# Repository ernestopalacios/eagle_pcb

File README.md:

eagle_pcb
=========

Diseños de placas

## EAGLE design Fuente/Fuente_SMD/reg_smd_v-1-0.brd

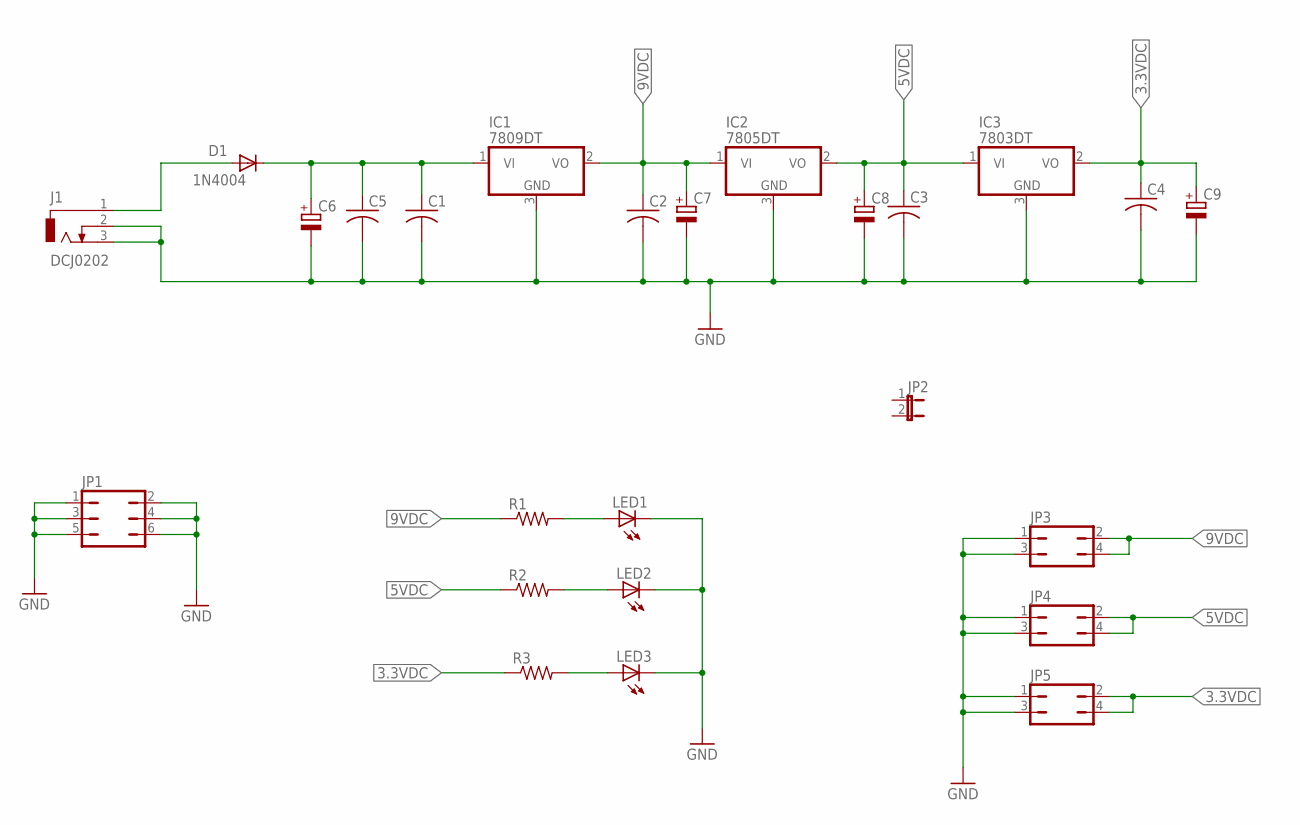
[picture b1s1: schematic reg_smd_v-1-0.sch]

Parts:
C1, C2, C3, C4, C5: C-USC1206; C1206
C6, C7, C8, C9: CPOL-EUE2.5-6; E2,5-6
D1: 1N4004; DO41-10
IC1: 7809DT; TO252
IC2: 7805DT; TO252
IC3: 7803DT; TO252
J1: DCJ0202
JP1: JP3Q
JP2: JP1E; JP1
JP3, JP4, JP5: JP2Q
LED1, LED2, LED3: LEDCHIPLED_1206; CHIPLED_1206
R1, R2, R3: R-US_M1206; M1206

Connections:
3.3VDC: C4.1, C9.+, IC3.2 (VO), JP5.2, JP5.4, R3.1
5VDC: C3.1, C8.+, IC2.2 (VO), IC3.1 (VI), JP4.2, JP4.4, R2.1
9VDC: C2.1, C7.+, IC1.2 (VO), IC2.1 (VI), JP3.2, JP3.4, R1.1
GND: C1.2, C2.2, C3.2, C4.2, C5.2, C6.-, C7.-, C8.-, C9.-, IC1.3 (GND), IC2.3 (GND), IC3.3 (GND), J1.2, J1.3, JP1.1, JP1.2, JP1.3, JP1.4, JP1.5, JP1.6, JP3.1, JP3.3, JP4.1, JP4.3, JP5.1, JP5.3, LED1.C, LED2.C, LED3.C
unnamed: LED1.A, R1.2
unnamed: LED2.A, R2.2
unnamed: LED3.A, R3.2
unnamed: D1.A, J1.1
unnamed: C1.1, C5.1, C6.+, D1.C, IC1.1 (VI)

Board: 2 copper layers, 25 parts (0 on the bottom side), 9 nets, no tracks yet.

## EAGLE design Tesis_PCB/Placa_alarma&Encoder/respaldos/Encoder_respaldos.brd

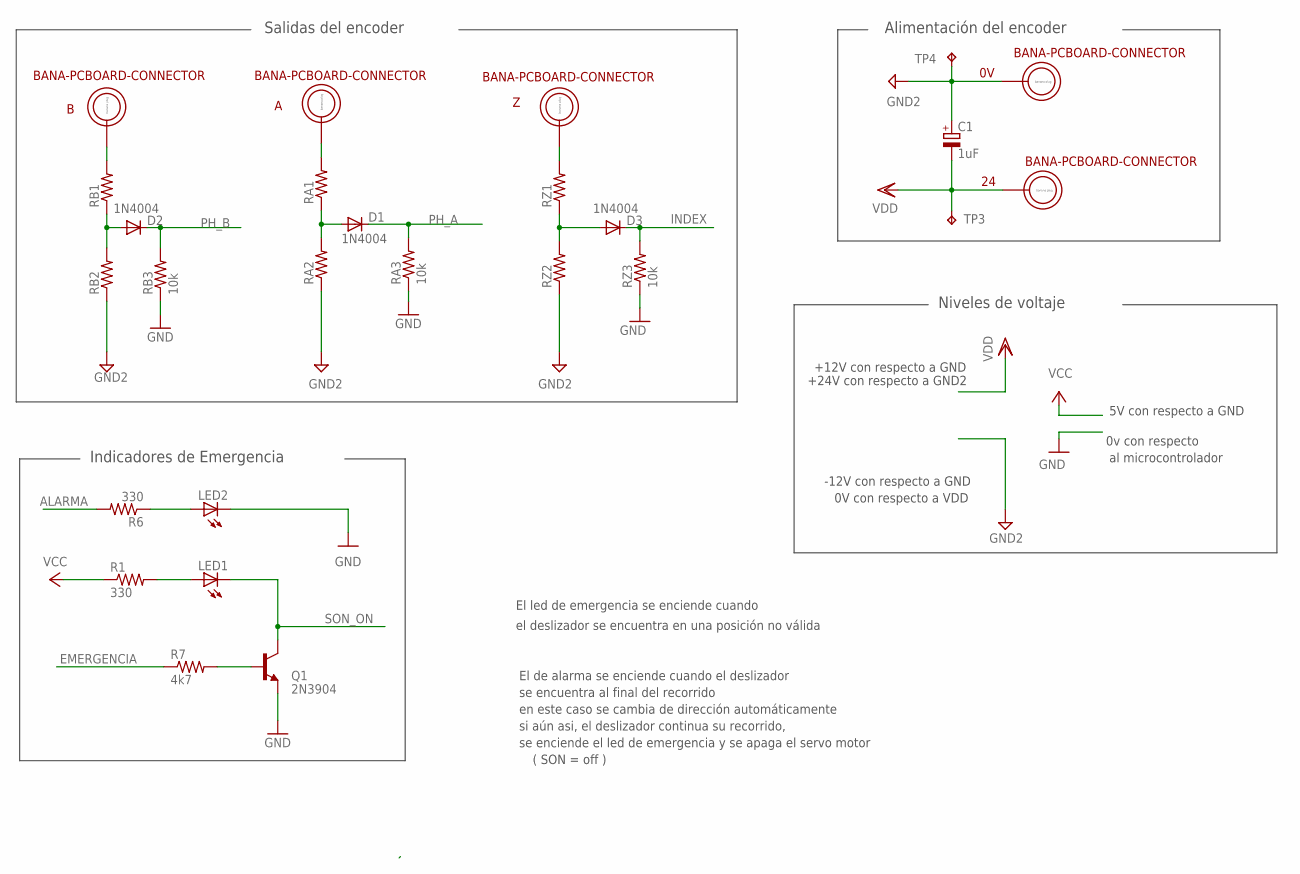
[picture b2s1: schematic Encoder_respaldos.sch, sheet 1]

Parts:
0V, 24: BANA-PCBOARD-CONNECTOR; BANA_PLUG
A: BANA-PCBOARD-CONNECTOR; BANA_PLUG
B: BANA-PCBOARD-CONNECTOR; BANA_PLUG
C1: 1uF; E2,5-6
D1, D2, D3: 1N4004; DO41-10
LED1, LED2: LED5MM
Q1: 2N3904; TO92
R1, R6: 330; 0204/7
R7: 4k7; 0204/7
RA1, RA2: R-US_0204/7; 0204/7
RA3: 10k; 0204/7
RB1, RB2: R-US_0204/7; 0204/7
RB3: 10k; 0204/7
RZ1, RZ2: R-US_0204/7; 0204/7
RZ3: 10k; 0204/7
TP3, TP4: TPB2,54; B2,54
Z: BANA-PCBOARD-CONNECTOR; BANA_PLUG

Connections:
ALARMA: R6.2; also elsewhere on the board
EMERGENCIA: R7.1; also elsewhere on the board
GND: LED2.K (C), Q1.3 (E), RA3.1, RB3.1, RZ3.1; also elsewhere on the board
GND2: 0V.P$1, C1.+, RA2.1, RB2.1, RZ2.1, TP4.TP; also elsewhere on the board
INDEX: D3.C, RZ3.2; also elsewhere on the board
unnamed: Q1.2 (B), R7.2
unnamed: LED1.A, R1.2
unnamed: LED2.A, R6.1
unnamed: D1.A, RA1.1, RA2.2
unnamed: D2.A, RB1.1, RB2.2
unnamed: RZ1.2, Z.P$1
unnamed: B.P$1, RB1.2
unnamed: A.P$1, RA1.2
unnamed: D3.A, RZ1.1, RZ2.2
PH_A: D1.C, RA3.2; also elsewhere on the board
PH_B: D2.C, RB3.2; also elsewhere on the board
SON_ON: LED1.K (C), Q1.1 (C); also elsewhere on the board
VCC: R1.1; also elsewhere on the board
VDD: 24.P$1, C1.-, TP3.TP; also elsewhere on the board

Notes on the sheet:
0v con respecto
5V con respecto a GND
+12V con respecto a GND
+24V con respecto a GND2
-12V con respecto a GND
0V con respecto a VDD
El led de emergencia se enciende cuando
el deslizador se encuentra en una posición no válida
El de alarma se enciende cuando el deslizador
se encuentra al final del recorrido
en este caso se cambia de dirección automáticamente
si aún asi, el deslizador continua su recorrido,
se enciende el led de emergencia y se apaga el servo motor
( SON = off )
Indicadores de Emergencia
Salidas del encoder
Alimentación del encoder
Niveles de voltaje
al microcontrolador

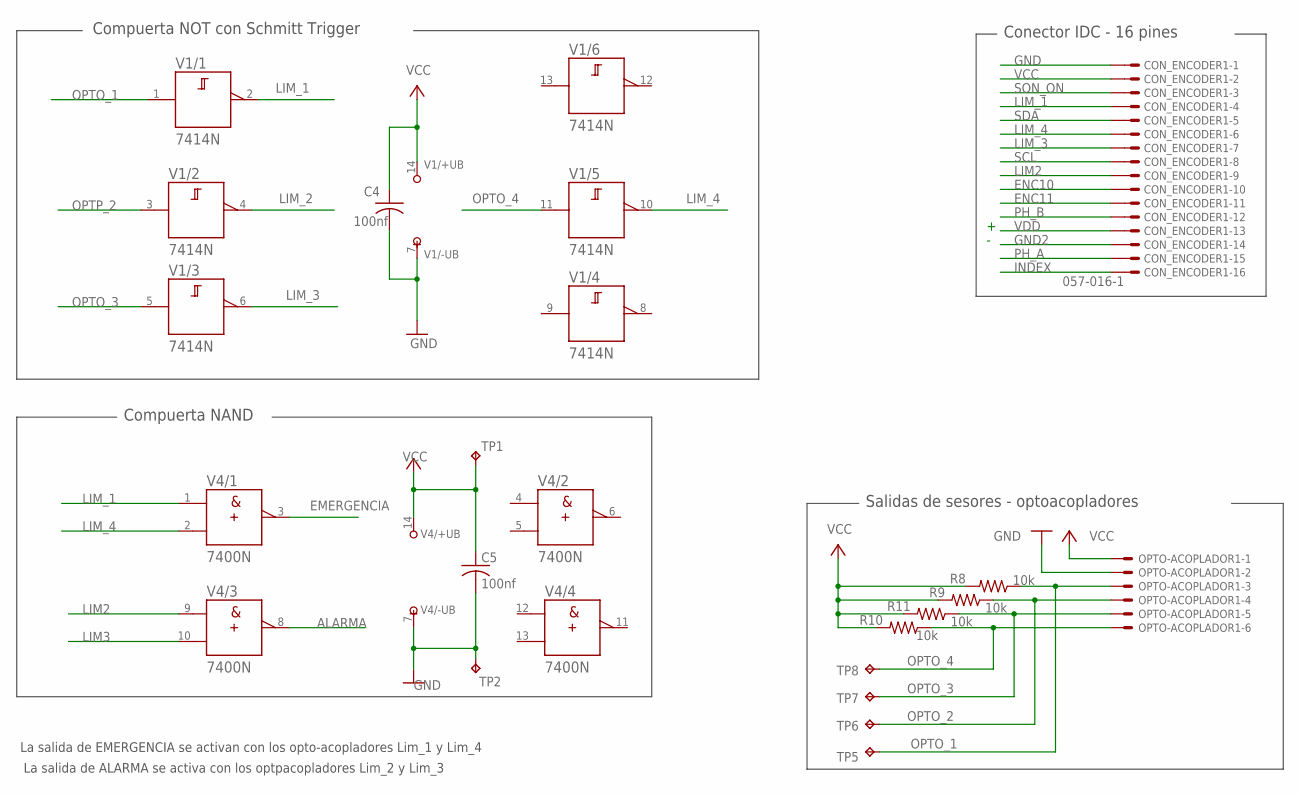
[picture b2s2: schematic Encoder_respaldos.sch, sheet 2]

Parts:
C4, C5: 100nf; C025-024X044
CON_ENCODER1: 057-016-1
OPTO-ACOPLADOR1: 22-23-2061
R8, R9, R10, R11: 10k; 0204/7
TP1, TP2, TP5, TP6, TP7, TP8: TPB2,54; B2,54
V1: 7414N; DIL14
V4: 7400N; DIL14

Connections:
ALARMA: V4.8 (Y); also elsewhere on the board
EMERGENCIA: V4.3 (Y); also elsewhere on the board
ENC10: CON_ENCODER1.10
ENC11: CON_ENCODER1.11
GND: C4.2, C5.2, CON_ENCODER1.1, OPTO-ACOPLADOR1.2, TP2.TP, V1.7 (-UB), V4.7 (-UB); also elsewhere on the board
GND2: CON_ENCODER1.14; also elsewhere on the board
INDEX: CON_ENCODER1.16; also elsewhere on the board
LIM2: CON_ENCODER1.9, V4.9 (A)
LIM3: V4.10 (B)
LIM_1: CON_ENCODER1.4, V1.2 (Y), V4.1 (A)
LIM_2: V1.4 (Y)
LIM_3: CON_ENCODER1.7, V1.6 (Y)
LIM_4: CON_ENCODER1.6, V1.10 (Y), V4.2 (B)
OPTO_1: OPTO-ACOPLADOR1.3, R8.1, TP5.TP, V1.1 (A)
OPTO_2: OPTO-ACOPLADOR1.4, R9.1, TP6.TP
OPTO_3: OPTO-ACOPLADOR1.5, R11.1, TP7.TP, V1.5 (A)
OPTO_4: OPTO-ACOPLADOR1.6, R10.1, TP8.TP, V1.11 (A)
OPTP_2: V1.3 (A)
PH_A: CON_ENCODER1.15; also elsewhere on the board
PH_B: CON_ENCODER1.12; also elsewhere on the board
SCL: CON_ENCODER1.8
SDA: CON_ENCODER1.5
SON_ON: CON_ENCODER1.3; also elsewhere on the board
VCC: C4.1, C5.1, CON_ENCODER1.2, OPTO-ACOPLADOR1.1, R8.2, R9.2, R10.2, R11.2, TP1.TP, V1.14 (+UB), V4.14 (+UB); also elsewhere on the board
VDD: CON_ENCODER1.13; also elsewhere on the board

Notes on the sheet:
Compuerta NAND
Compuerta NOT con Schmitt Trigger
Conector IDC - 16 pines
Salidas de sesores - optoacopladores
La salida de EMERGENCIA se activan con los opto-acopladores Lim_1 y Lim_4
La salida de ALARMA se activa con los optpacopladores Lim_2 y Lim_3

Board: 2 copper layers, 42 parts (0 on the bottom side), 27 nets, no tracks yet.

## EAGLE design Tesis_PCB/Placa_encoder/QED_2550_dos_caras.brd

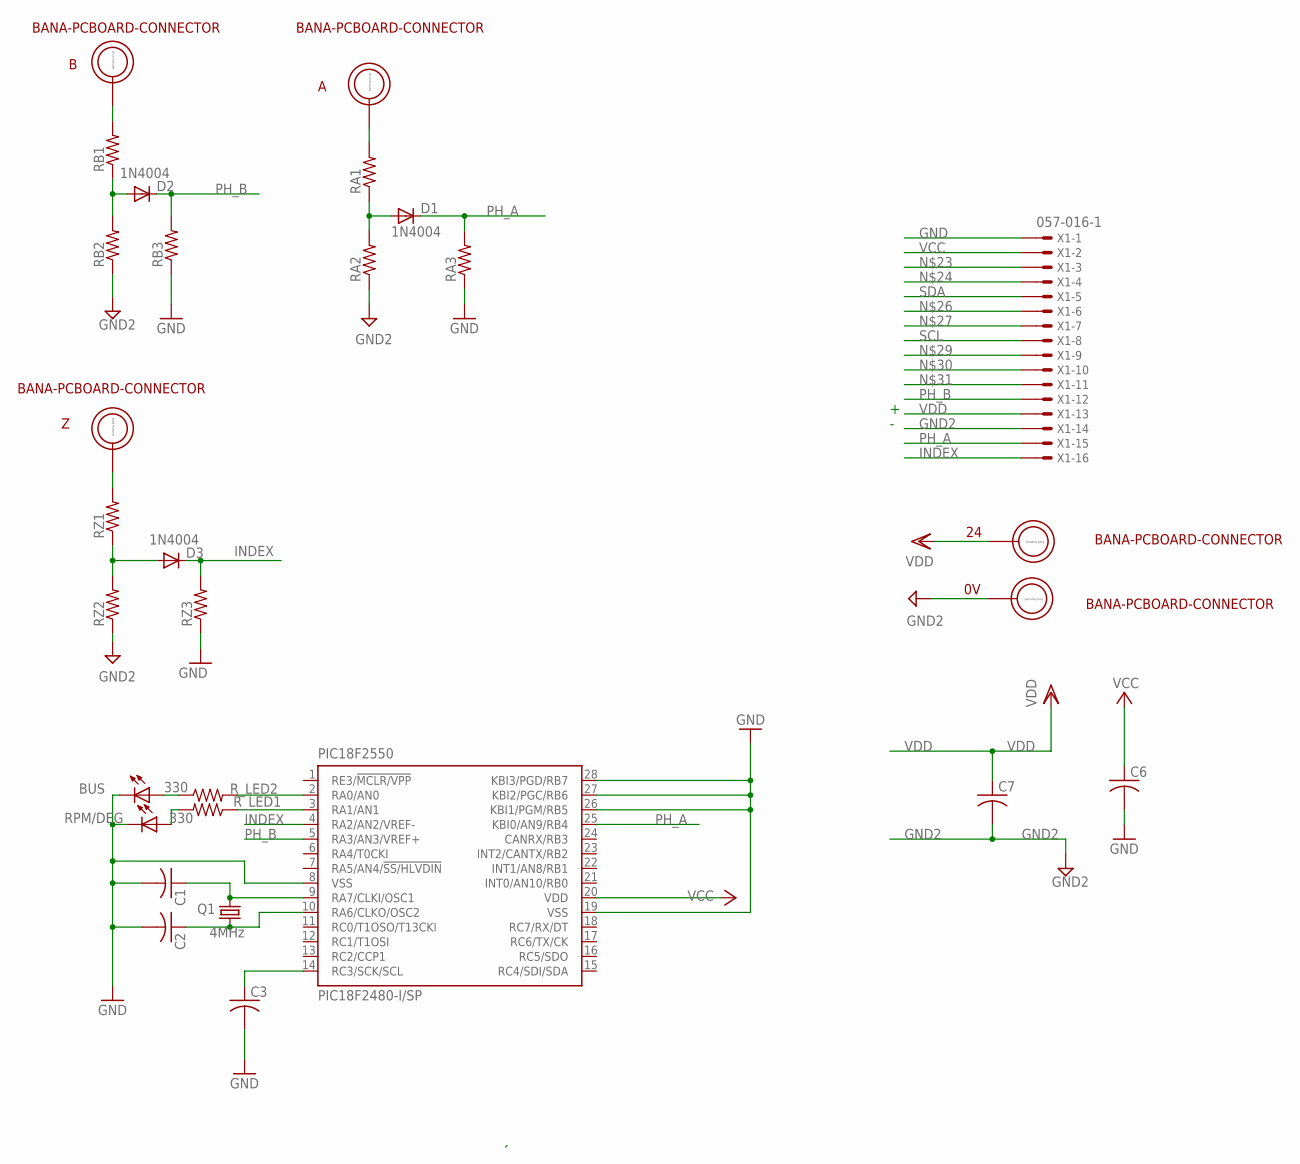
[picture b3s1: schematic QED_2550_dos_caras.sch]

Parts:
0V, 24: BANA-PCBOARD-CONNECTOR; BANA_PLUG
A: BANA-PCBOARD-CONNECTOR; BANA_PLUG
B: BANA-PCBOARD-CONNECTOR; BANA_PLUG
BUS: LED5MM
C1, C2, C3: C-US025-024X044; C025-024X044
C6, C7: C-US025-030X050; C025-030X050
D1, D2, D3: 1N4004; DO41-10
PIC18F2550: PIC18F2480-I/SP; DIL28-3
Q1: 4MHz; HC49/S
RA1, RA2, RA3: R-US_0204/7; 0204/7
RB1, RB2, RB3: R-US_0204/7; 0204/7
RPM/DEG: LED5MM
RZ1, RZ2, RZ3: R-US_0204/7; 0204/7
R_LED1, R_LED2: 330; 0204/7
X1: 057-016-1
Z: BANA-PCBOARD-CONNECTOR; BANA_PLUG

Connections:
GND: BUS.K (C), C1.2, C2.2, C3.2, C6.2, PIC18F2550.8 (VSS), PIC18F2550.19 (VSS), PIC18F2550.26 (KBI1/PGM/RB5), PIC18F2550.27 (KBI2/PGC/RB6), PIC18F2550.28 (KBI3/PGD/RB7), RA3.1, RB3.1, RPM/DEG.K (C), RZ3.1, X1.1
GND2: 0V.P$1, C7.2, RA2.1, RB2.1, RZ2.1, X1.14
INDEX: D3.C, PIC18F2550.4 (RA2/AN2/VREF-), RZ3.2, X1.16
unnamed: C1.1, PIC18F2550.9 (RA7/CLKI/OSC1), Q1.2
unnamed: C2.1, PIC18F2550.10 (RA6/CLKO/OSC2), Q1.1
unnamed: C3.1, PIC18F2550.14 (RC3/SCK/SCL)
unnamed: PIC18F2550.2 (RA0/AN0), R_LED2.2
unnamed: BUS.A, R_LED2.1
unnamed: PIC18F2550.3 (RA1/AN1), R_LED1.1
unnamed: RPM/DEG.A, R_LED1.2
unnamed: D1.A, RA1.1, RA2.2
unnamed: D2.A, RB1.1, RB2.2
unnamed: RZ1.2, Z.P$1
unnamed: B.P$1, RB1.2
unnamed: A.P$1, RA1.2
unnamed: D3.A, RZ1.1, RZ2.2
PH_A: D1.C, PIC18F2550.25 (KBI0/AN9/RB4), RA3.2, X1.15
PH_B: D2.C, PIC18F2550.5 (RA3/AN3/VREF+), RB3.2, X1.12
SCL: X1.8
SDA: X1.5
VCC: C6.1, PIC18F2550.20 (VDD), X1.2
VDD: 24.P$1, C7.1, X1.13

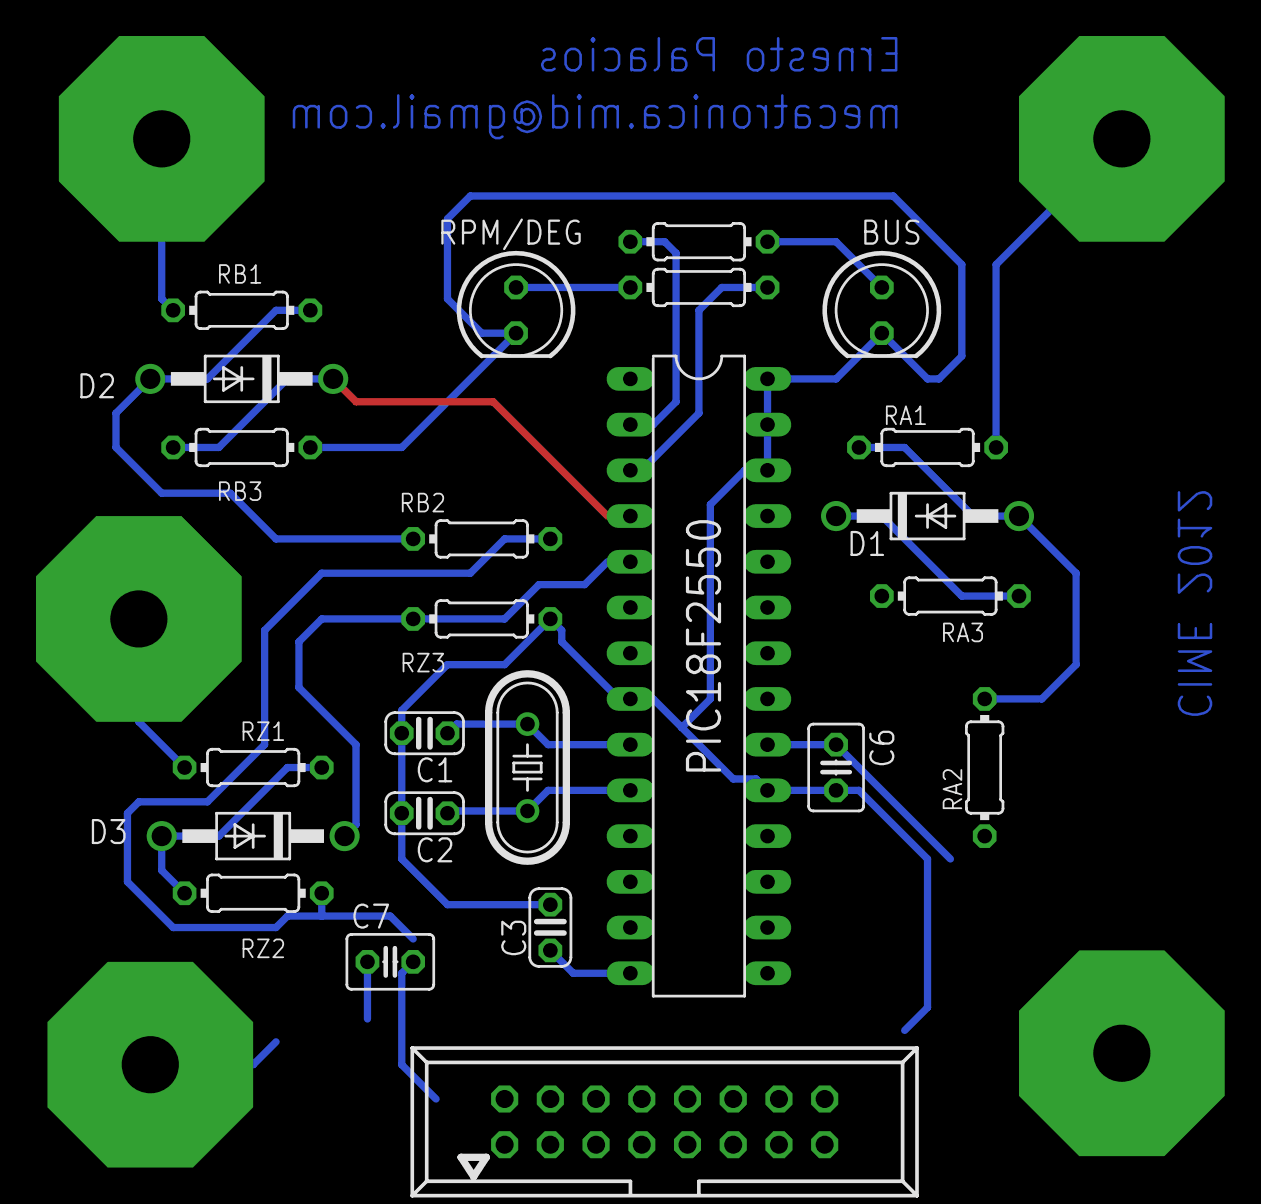
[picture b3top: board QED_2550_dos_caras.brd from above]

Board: 2 copper layers, 29 parts (0 on the bottom side), 20 nets.

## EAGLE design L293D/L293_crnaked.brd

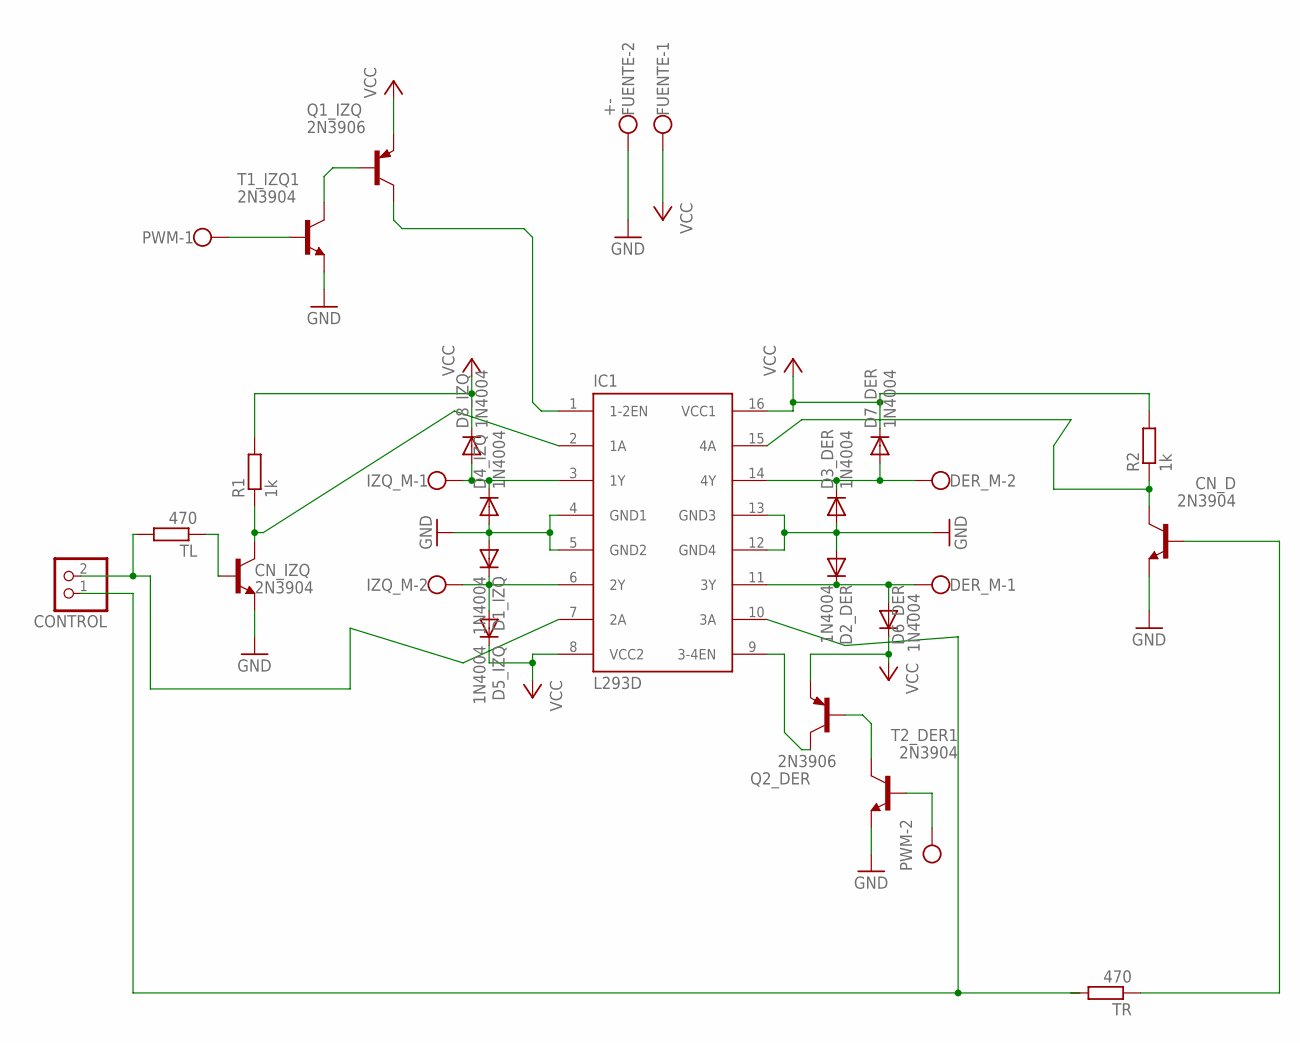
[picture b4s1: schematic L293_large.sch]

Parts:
CN_D: 2N3904; TO92
CN_IZQ: 2N3904; TO92
CONTROL: PINHD-1X2/90; 1X02/90
D1_IZQ, D2_DER, D3_DER, D4_IZQ, D5_IZQ, D6_DER, D7_DER, D8_IZQ: 1N4004; DO41-10
DER_M: W237-02P; W237-132
FUENTE: +-; W237-132
IC1: L293D; DIL16
IZQ_M: W237-02P; W237-132
PWM: W237-02P; W237-132
Q1_IZQ, Q2_DER: 2N3906; TO92
R1, R2: 1k; 0207/5V
T1_IZQ1, T2_DER1: 2N3904; TO92
TL: 470; 0207/5V
TR: 470; 0207/5V

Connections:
GND: CN_D.3 (E), CN_IZQ.3 (E), D1_IZQ.A, D2_DER.A, D3_DER.A, D4_IZQ.A, FUENTE.2, IC1.4 (GND1), IC1.5 (GND2), IC1.12 (GND4), IC1.13 (GND3), T1_IZQ1.3 (E), T2_DER1.3 (E); also elsewhere on the board
unnamed: D2_DER.C, D6_DER.A, DER_M.1, IC1.11 (3Y)
unnamed: D3_DER.C, D7_DER.A, DER_M.2, IC1.14 (4Y)
unnamed: D1_IZQ.C, D5_IZQ.A, IC1.6 (2Y), IZQ_M.2
unnamed: D4_IZQ.C, D8_IZQ.A, IC1.3 (1Y), IZQ_M.1
unnamed: CONTROL.2, IC1.7 (2A), TL.2
unnamed 6: CN_IZQ.2 (B), TL.1; also elsewhere on the board
unnamed 7: CN_IZQ.1 (C), IC1.2 (1A), R1.1; also elsewhere on the board
unnamed 8: CN_D.2 (B), TR.1; also elsewhere on the board
unnamed 9: CN_D.1 (C), IC1.15 (4A), R2.1; also elsewhere on the board
unnamed: Q1_IZQ.2 (B), T1_IZQ1.1 (C)
unnamed: IC1.1 (1-2EN), Q1_IZQ.1 (C)
unnamed: CONTROL.1, IC1.10 (3A), TR.2
unnamed: PWM.1, T1_IZQ1.2 (B)
unnamed: Q2_DER.2 (B), T2_DER1.1 (C)
unnamed: PWM.2, T2_DER1.2 (B)
unnamed: IC1.9 (3-4EN), Q2_DER.1 (C)
VCC: D5_IZQ.C, D6_DER.C, D7_DER.C, D8_IZQ.C, FUENTE.1, IC1.8 (VCC2), IC1.16 (VCC1), Q1_IZQ.3 (E), Q2_DER.3 (E), R1.2, R2.2

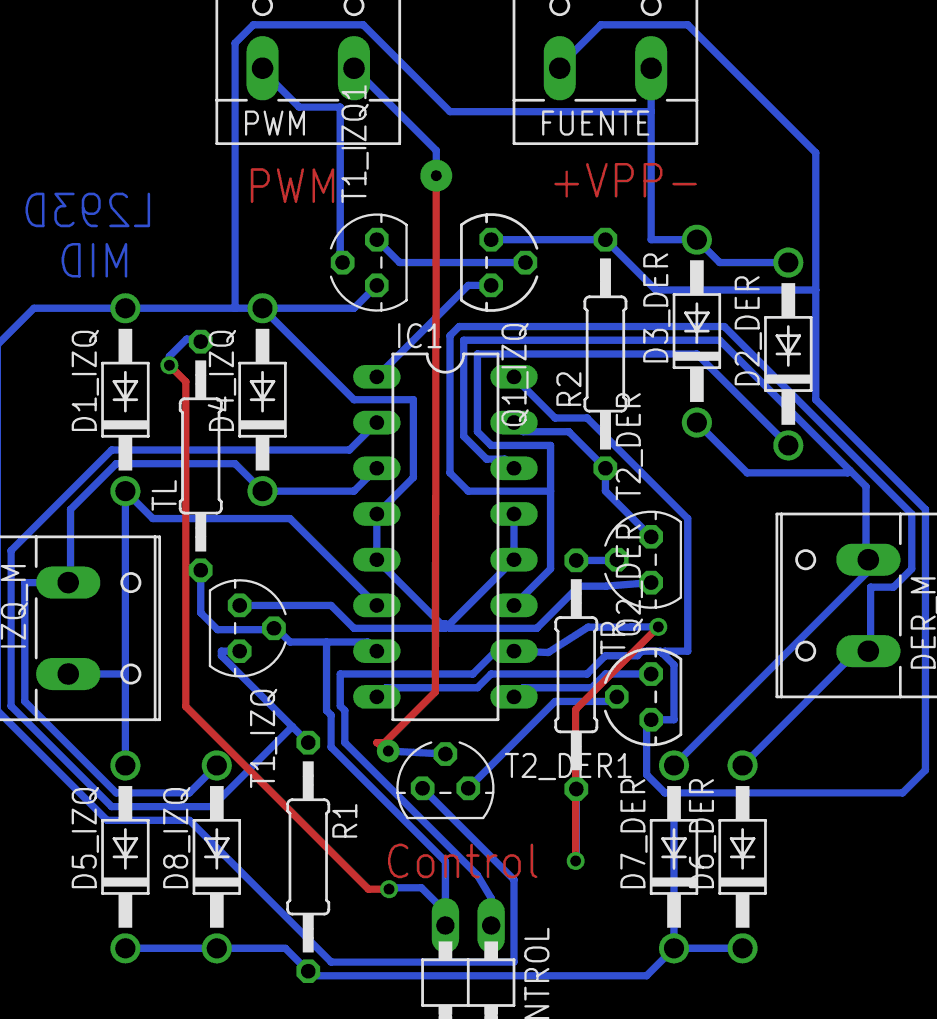
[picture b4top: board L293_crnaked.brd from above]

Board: 2 copper layers, 24 parts (0 on the bottom side), 18 nets.

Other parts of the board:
T1_IZQ, T2_DER: 2N3904; TO92

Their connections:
GND: T1_IZQ.3, T2_DER.3; also elsewhere on the board
unnamed 6: T1_IZQ.2; also elsewhere on the board
unnamed 7: T1_IZQ.1; also elsewhere on the board
unnamed 8: T2_DER.2; also elsewhere on the board
unnamed 9: T2_DER.1; also elsewhere on the board

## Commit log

2014-08-28 Archivos Històricos
